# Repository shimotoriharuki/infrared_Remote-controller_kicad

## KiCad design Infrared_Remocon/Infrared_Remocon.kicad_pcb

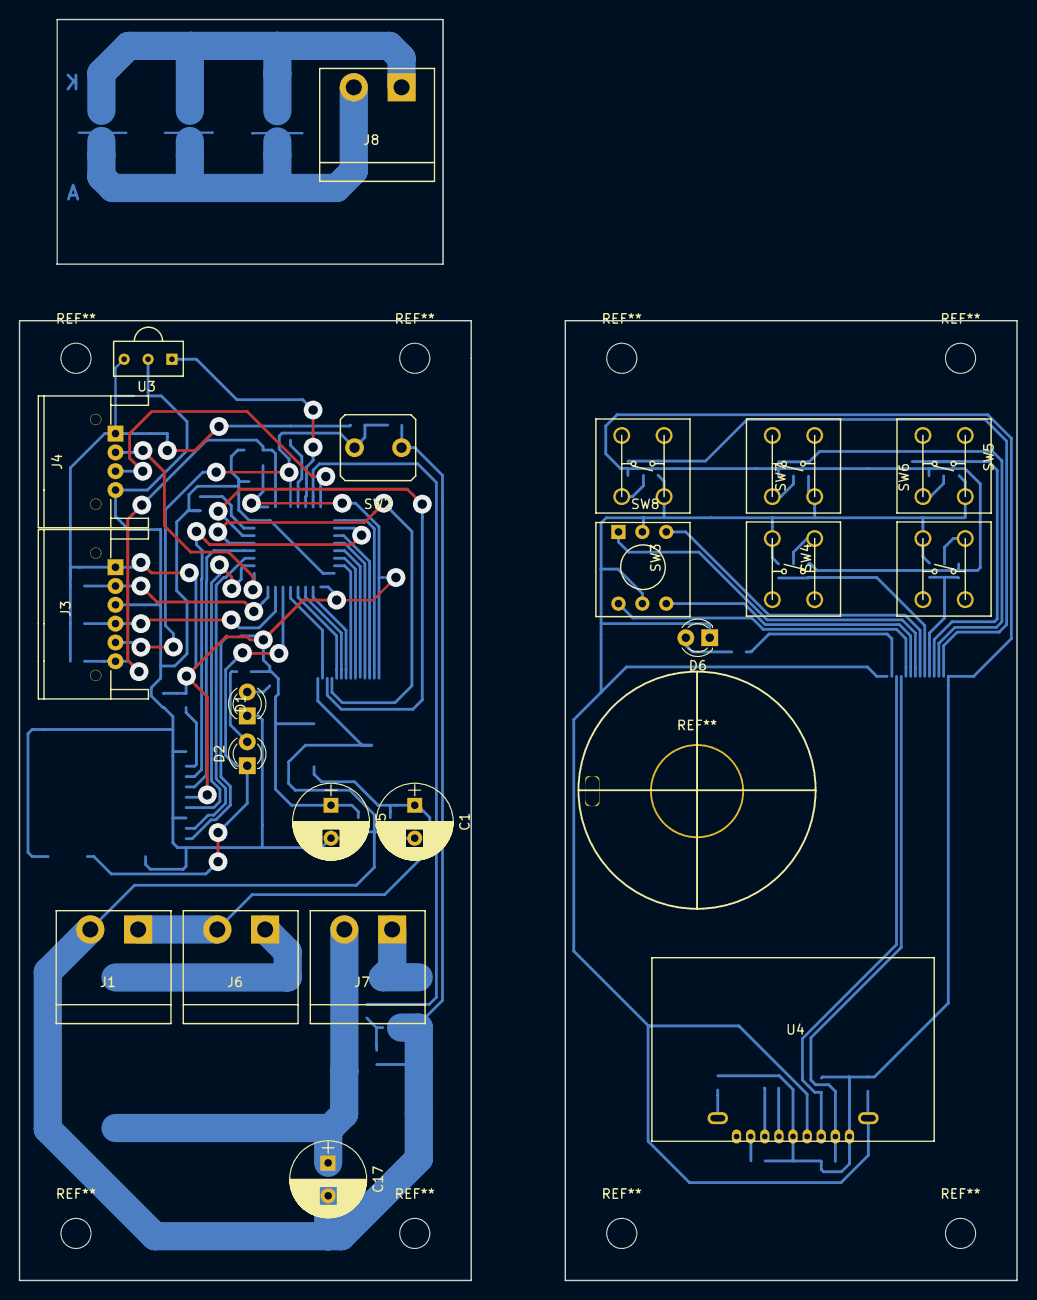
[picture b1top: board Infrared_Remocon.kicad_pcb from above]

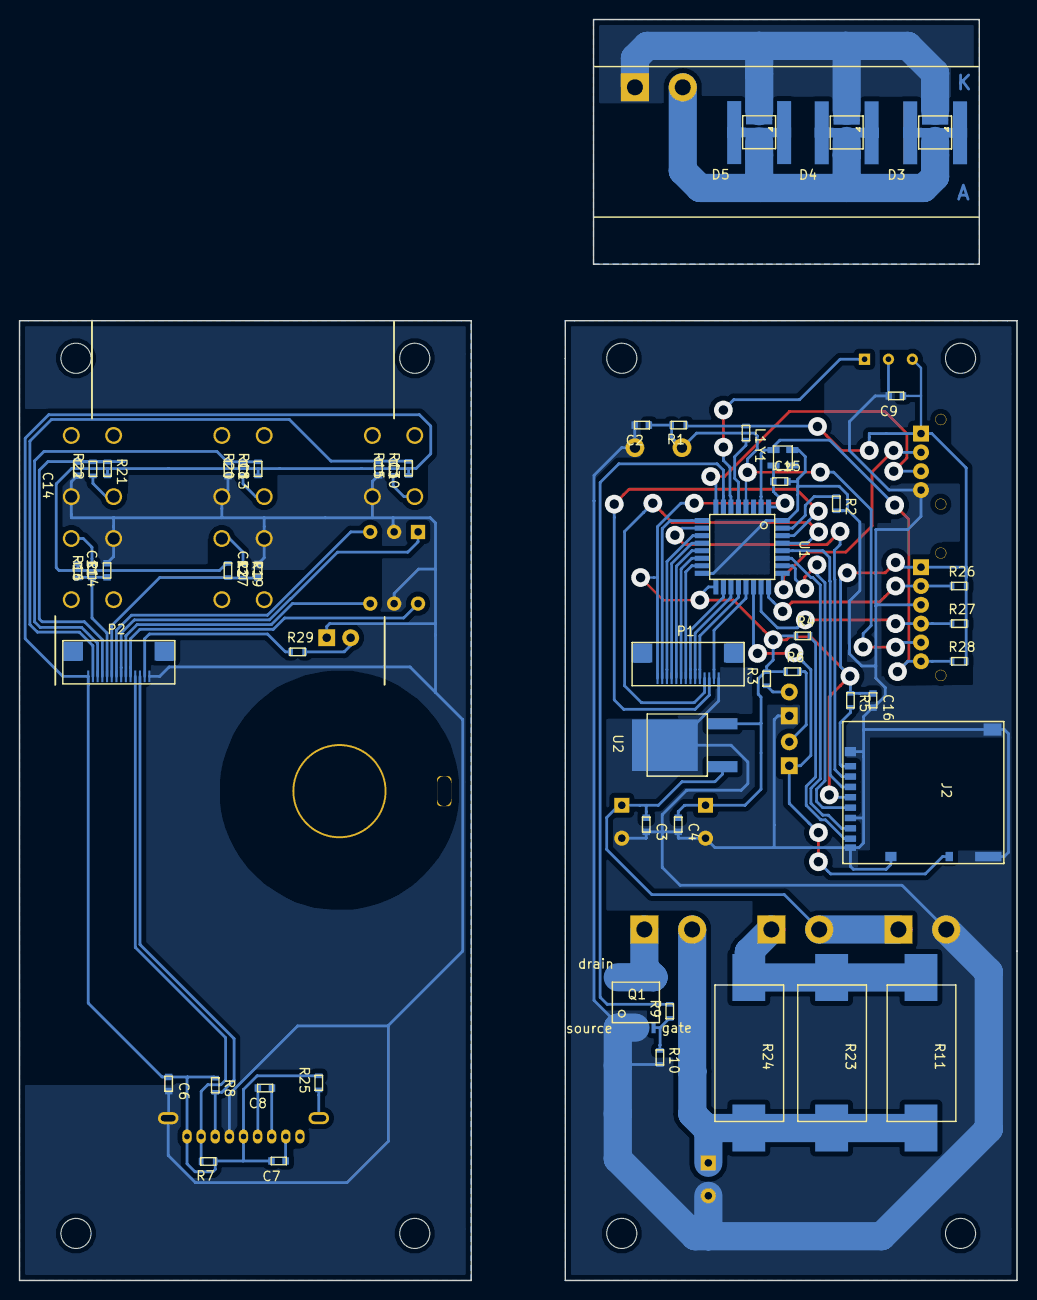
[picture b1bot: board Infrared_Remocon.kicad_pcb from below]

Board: 2 copper layers, 106.0 x 134.0 mm, 74 parts (51 on the bottom side), 64 nets.

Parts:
C1, C5: 100u; CP_Radial_D8.0mm_P3.50mm
C2, C7, C8, C10, C11, C12, C13, C14: 1u; C_1608_HandSolderring
C3, C4, C6, C16: 0.1u; C_1608_HandSolderring
C9: 4.7u; C_1608_HandSolderring
C15: 0.1; C_1608_HandSolderring
C17: CP; CP_Radial_D8.0mm_P3.50mm
D1, D2, D6: LED; LED_D3.0mm
D3, D4, D5: SFH 4715AS; SFH4715AS
J1: batt_conn; terminal_block_2p
J2: Micro_SD_Card_Det_Hirose_DM3AT; micro_SDcard
J3: PA_SIDE; PA_SIDE_6p
J4: PA_SIDE; PA_SIDE_4p
J6, J7: Terminal_Female; terminal_block_2p
J8: Terminal_Male; terminal_block_2p
L1: Ferrite_Bead_Small; R_1608_HandSoldering
P1, P2: CN-FFC(0.5)14PD; CN-FFC-SMT2(CN-FFC(0.5)14PD)
Q1: RSS100N03
R1: 150k; R_1608_HandSoldering
R2, R7, R8, R13, R14, R17, R18, R21: 10k; R_1608_HandSoldering
R3, R29: 330; R_1608_HandSoldering
R4, R5: 47k; R_1608_HandSoldering
R6: 1k; R_1608_HandSoldering
R9: 10; R_1608_HandSoldering
R10: 12k; R_1608_HandSoldering
R11, R23, R24: 4.7; SMW54R7JT
R15, R16, R19, R20, R22: 100; R_1608_HandSoldering
R25: 20; R_1608_HandSoldering
R26, R27, R28: 100k; R_1608_HandSoldering
SW2: SW_Push; tact_switch
SW3, SW4, SW5, SW6, SW7: SW_Push; TS-AGGNH-G
SW8: SW_Coded_SH-7050; rotary_switch
U1: STM32F303K8; STM32F303K8T6
U2: NJM2845DL1
U3: PL-IRM1261-C438
U4: AQM0802A_Backlight; AQM0802A_backlight
Y1: ASCO-8.000MHZ-EK-T3; ASDMB-8.000MHZ-LY-T

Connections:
3.3_A: C4.1, C5.1, C9.1, C15.1, C16.1, J2.4, J3.1, J4.1, L1.1, P1.1, R1.1, R3.2, R4.1, R5.1, R6.1, R26.2, R27.2, R28.2, U1.1, U1.17, U2.3, U3.3, Y1.4
3.3_B: C6.1, C7.2, P2.1, R7.1, R8.1, R13.1, R14.1, R17.1, R18.1, R21.2, R25.2, U4.5, U4.9
+BATT: C1.1, C3.1, J1.1, J6.2, U2.1
CARD_DITECTION: D2.1, J2.10, U1.22
CS: J2.2, U1.10
GND_A: C1.2, C2.2, C3.2, C4.2, C5.2, C9.2, C15.2, C16.2, C17.2, D1.1, J1.2, J2.6, J2.9, J2.11, J2.12, J2.13, J2.14, J3.3, J4.4, P1.14, Q1.1, R2.2, R10.2, SW2.1, U1.16, U1.32, U2.2, U3.2, Y1.2
GND_B: C6.2, C10.2, C11.2, C12.2, C13.2, C14.2, D6.1, P2.14, SW3.2, SW4.2, SW5.2, SW6.2, SW7.2, SW8.C, U4.6, U4.K
IR_IN: U1.6, U3.1
IR_LED: R9.2, U1.7
LED_A: P1.13, U1.21
LED_B: P2.13, R29.1
MISO: J2.7, U1.27
MOSI: J2.3, U1.28
NRST: C2.1, J3.5, R1.2, SW2.2, U1.4
unnamed: C7.1, U4.2
unnamed: C8.1, U4.3
unnamed: C8.2, U4.4
unnamed: C17.1, J7.2, R11.2, R23.2, R24.2
unnamed: D1.2, R3.1
unnamed: D2.2, R6.2
unnamed: D3.1, D4.1, D5.1, J8.1
unnamed: D3.2, D4.2, D5.2, J8.2
unnamed: D6.2, R29.2
unnamed: J2.1, R5.2
unnamed: J2.8, R4.2
unnamed: J6.1, R11.1, R23.1, R24.1
unnamed: J7.1, Q1.3
unnamed: L1.2, U1.5
unnamed: Q1.2, R9.1, R10.1
unnamed: R2.1, U1.31
unnamed: R15.1, SW3.1
unnamed: R16.2, SW6.1
unnamed: R19.1, SW7.1
unnamed: R20.1, SW4.1
unnamed: R22.1, SW5.1
unnamed: R25.1, U4.A
OSC_IN: J3.6, R28.1, U1.2, Y1.3
RS1_A: P1.8, U1.18
RS1_B: P2.8, SW8.1
RS2_A: P1.9, U1.19
RS2_B: P2.9, SW8.2
RS4_A: P1.10, U1.20
RS4_B: P2.10, SW8.4
RS8_A: P1.7, U1.15
RS8_B: P2.7, SW8.8
RX: J4.2, U1.25
SCK: J2.5, U1.26
SCL_A: P1.11, U1.29
SCL_B: P2.11, R7.2, U4.8
SDA_A: P1.12, U1.30
SDA_B: P2.12, R8.2, U4.7
SW1_A: P1.2, U1.9
SW1_B: C10.1, P2.2, R13.2, R15.2
SW2_A: P1.3, U1.11
SW2_B: C13.1, P2.3, R18.2, R20.2
SW3_A: P1.4, U1.12
SW3_B: C14.1, P2.4, R21.1, R22.2
SW4_A: P1.5, U1.13
SW4_B: C11.1, P2.5, R14.2, R16.1
SW5_A: P1.6, U1.14
SW5_B: C12.1, P2.6, R17.2, R19.2
TCK: J3.2, R26.1, U1.24
TMS: J3.4, R27.1, U1.23
TX: J4.3, U1.8

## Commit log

2021-03-22 init
2021-03-22 Create LICENSE
